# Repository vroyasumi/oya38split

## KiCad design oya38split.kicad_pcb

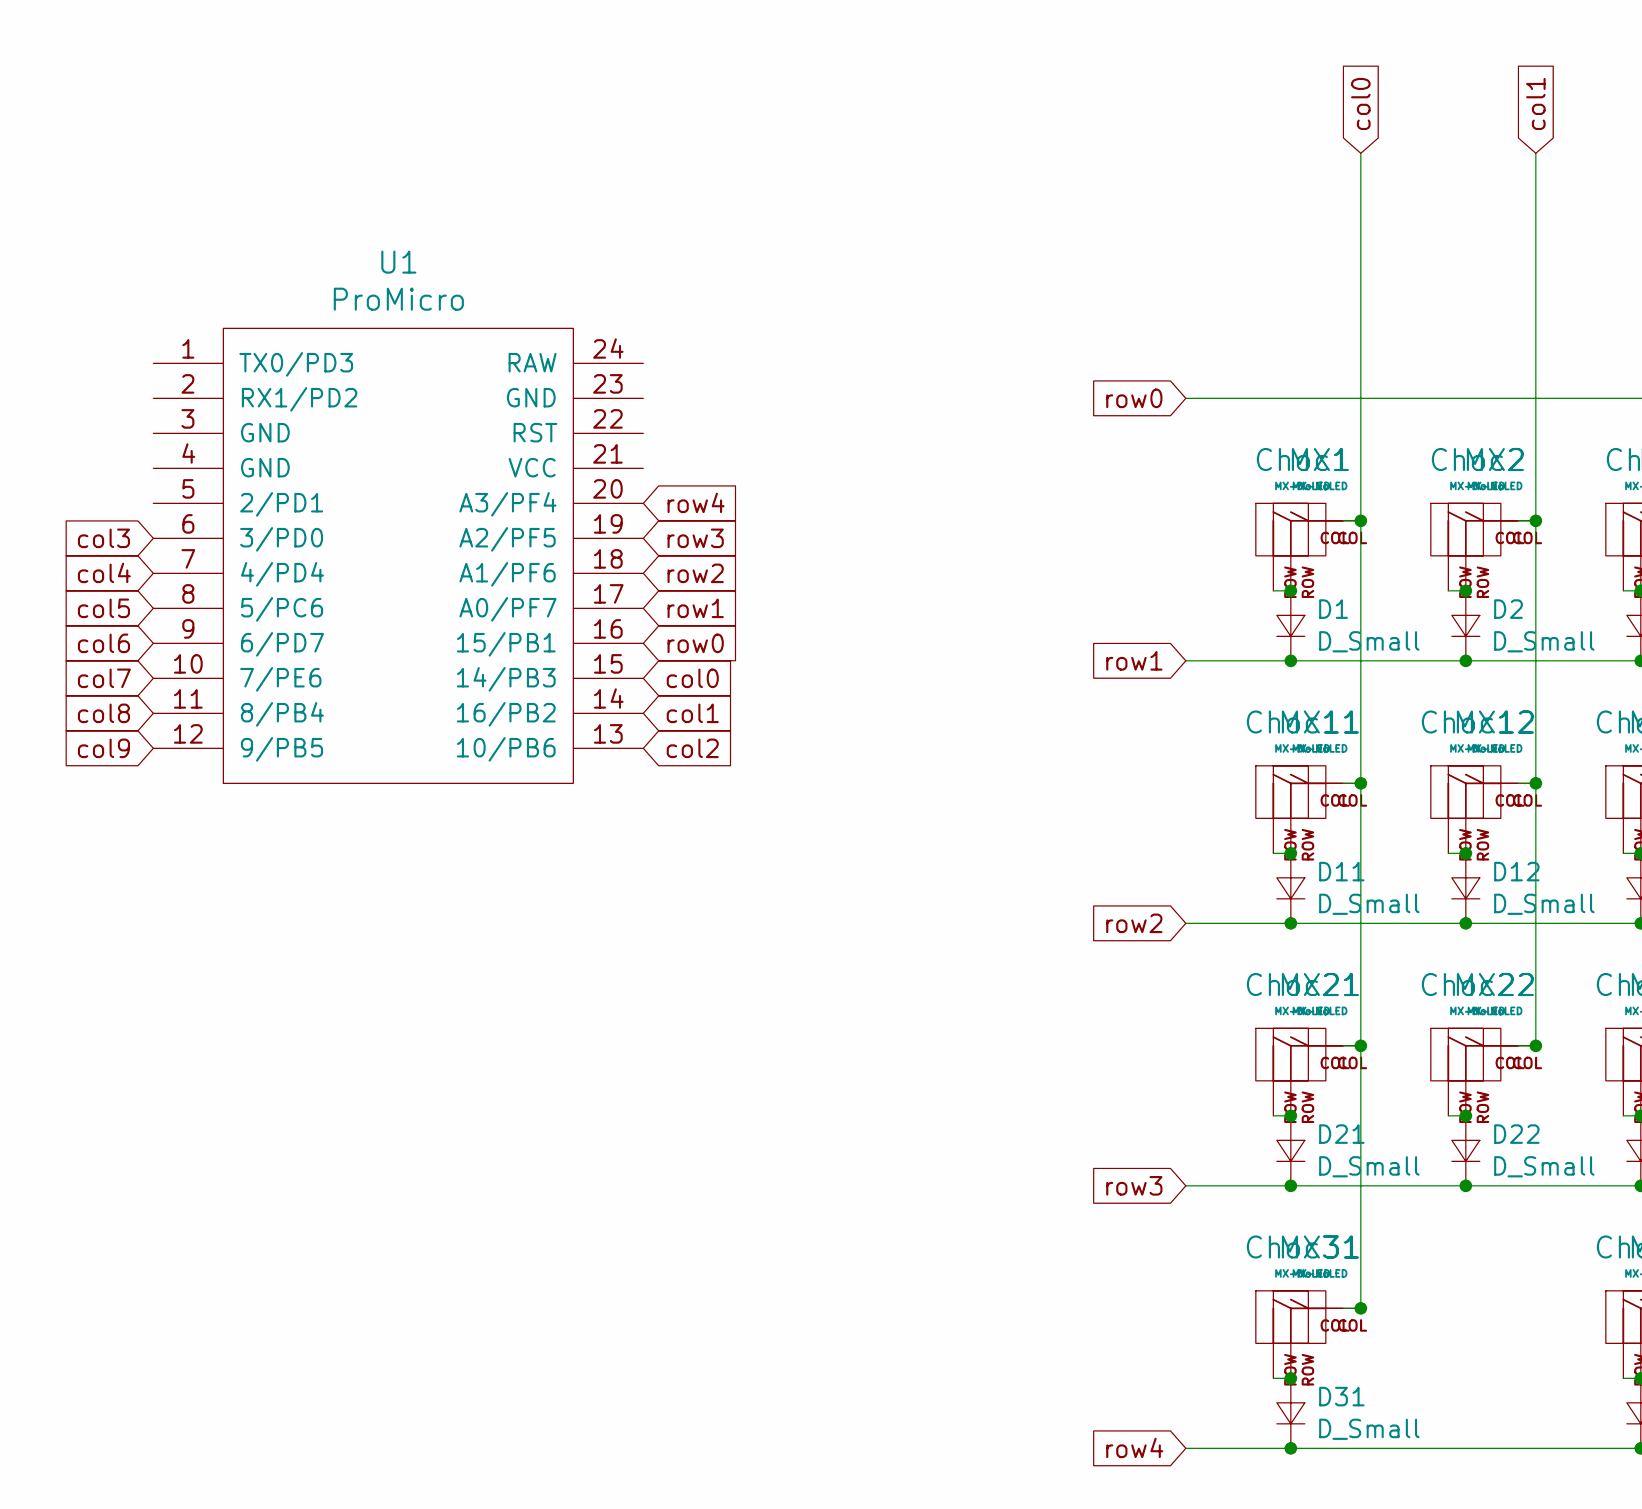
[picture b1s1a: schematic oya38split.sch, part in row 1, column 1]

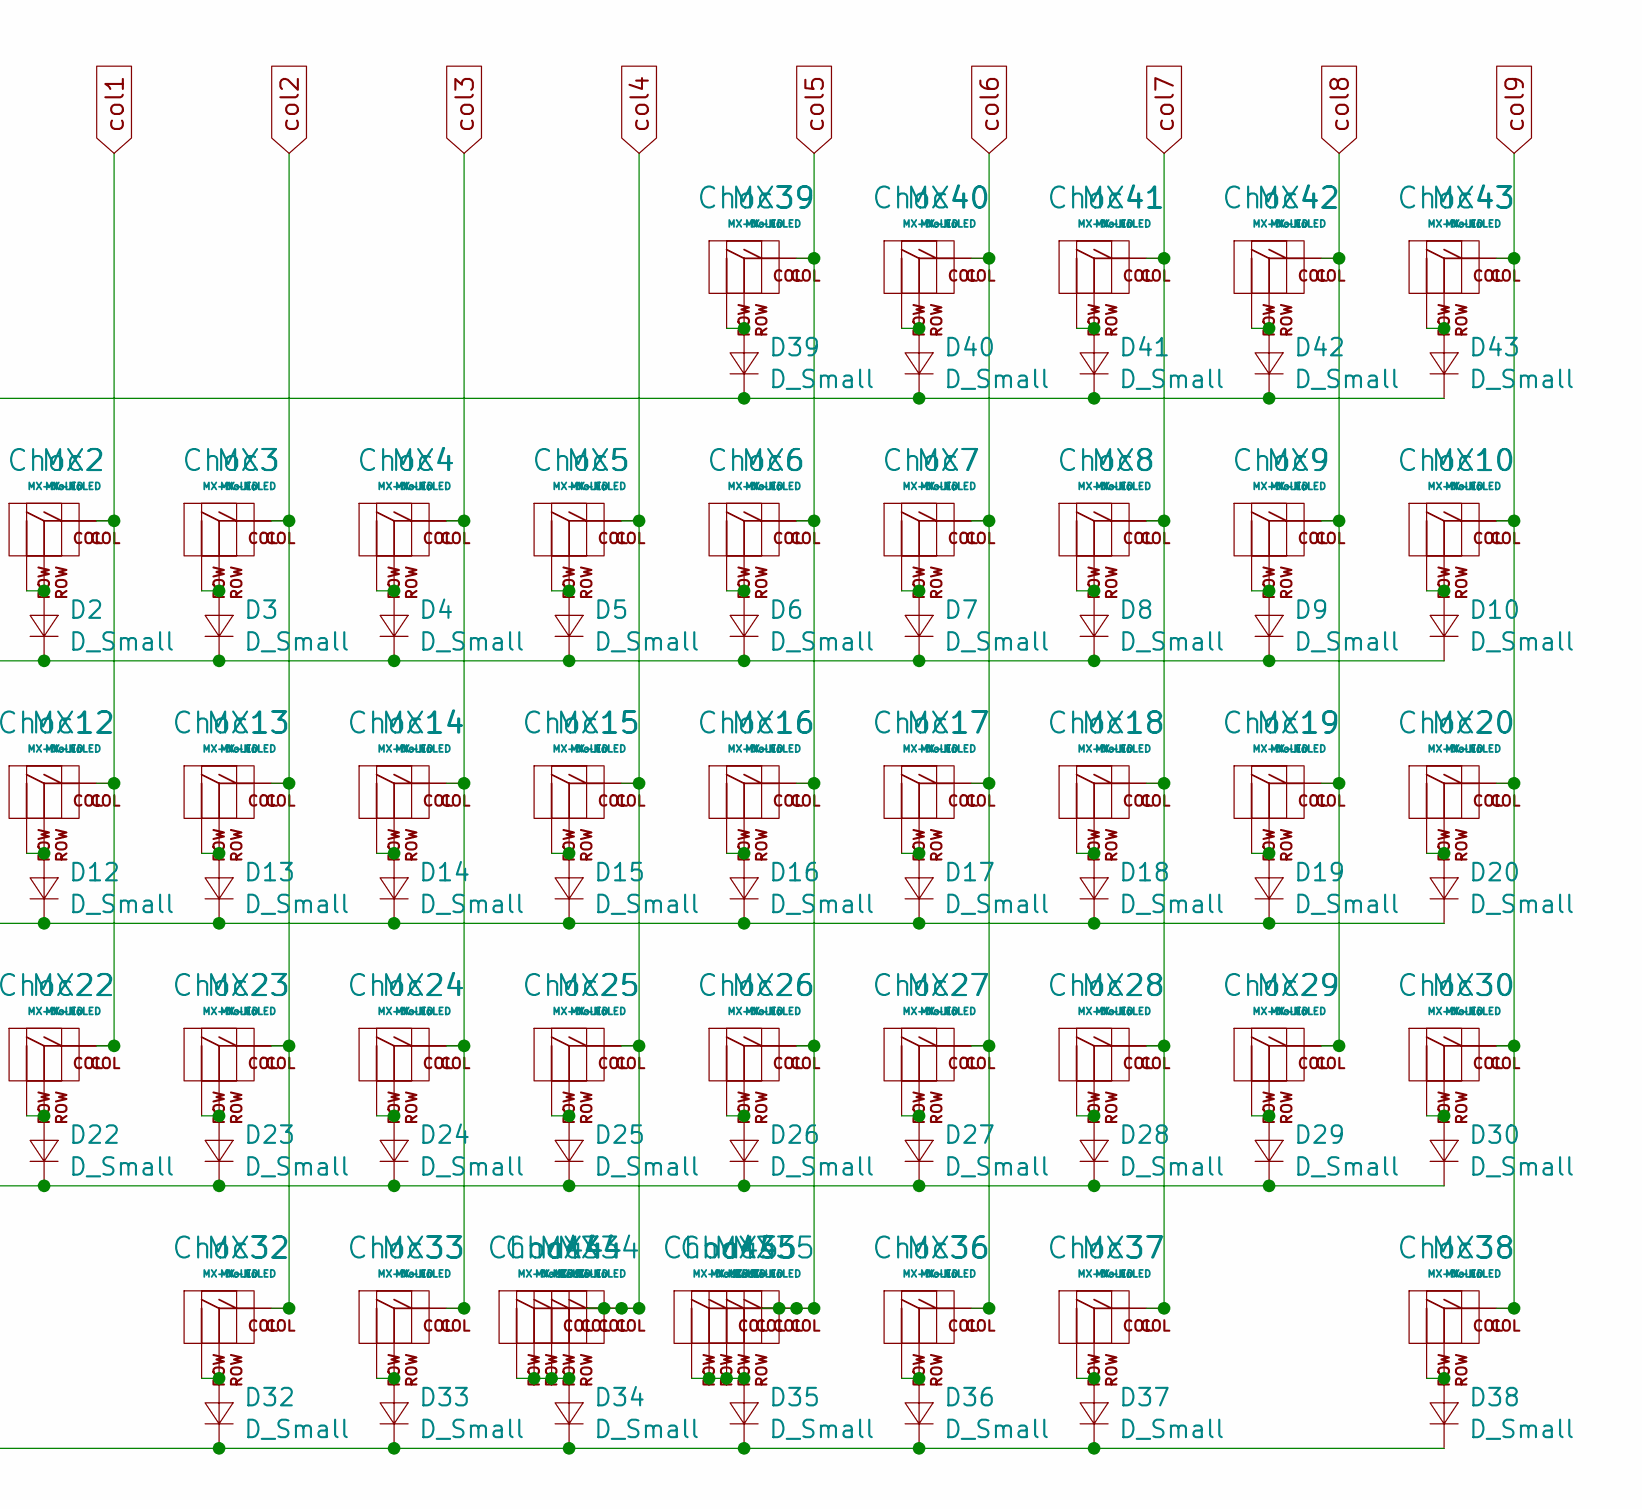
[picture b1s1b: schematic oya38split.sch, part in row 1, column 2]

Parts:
Choc1, Choc2, Choc3, Choc4, Choc5, Choc6, Choc7, Choc8, Choc9, Choc10, Choc11, Choc12, Choc13, Choc14, Choc15, Choc16, Choc17, Choc18, Choc19, Choc20, Choc21, Choc22, Choc23, Choc24, Choc25, Choc26, Choc27, Choc28, Choc29, Choc30, Choc31, Choc32, Choc33, Choc34, Choc35, Choc36, Choc37, Choc38, Choc39, Choc40, Choc41, Choc42, Choc43, Choc44, Choc45: MX-NoLED; ChocV1_V2_Hotswap
D1, D2, D3, D4, D5, D6, D7, D8, D9, D10, D11, D12, D13, D14, D15, D16, D17, D18, D19, D20, D21, D22, D23, D24, D25, D26, D27, D28, D29, D30, D31, D32, D33, D34, D35, D36, D37, D38, D39, D40, D41, D42, D43: D_Small; D_0805
MX1, MX2, MX3, MX4, MX5, MX6, MX7, MX8, MX9, MX10, MX11, MX12, MX13, MX14, MX15, MX16, MX17, MX18, MX19, MX20, MX21, MX22, MX23, MX24, MX25, MX26, MX27, MX28, MX29, MX30, MX31, MX32, MX33, MX34, MX35, MX36, MX37, MX38, MX39, MX40, MX41, MX42, MX43: MX-NoLED; MXOnly-1U-Hotswap
MX44, MX45: MX-NoLED; MXOnly-2U-Hotswap
U1: ProMicro; ArduinoProMicro-ZigZag

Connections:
unnamed: Choc1.2 (ROW), D1.2 (A), MX1.2 (ROW)
unnamed: Choc2.2 (ROW), D2.2 (A), MX2.2 (ROW)
unnamed: Choc3.2 (ROW), D3.2 (A), MX3.2 (ROW)
unnamed: Choc4.2 (ROW), D4.2 (A), MX4.2 (ROW)
unnamed: Choc5.2 (ROW), D5.2 (A), MX5.2 (ROW)
unnamed: Choc6.2 (ROW), D6.2 (A), MX6.2 (ROW)
unnamed: Choc7.2 (ROW), D7.2 (A), MX7.2 (ROW)
unnamed: Choc8.2 (ROW), D8.2 (A), MX8.2 (ROW)
unnamed: Choc9.2 (ROW), D9.2 (A), MX9.2 (ROW)
unnamed: Choc10.2 (ROW), D10.2 (A), MX10.2 (ROW)
unnamed: Choc11.2 (ROW), D11.2 (A), MX11.2 (ROW)
unnamed: Choc12.2 (ROW), D12.2 (A), MX12.2 (ROW)
unnamed: Choc13.2 (ROW), D13.2 (A), MX13.2 (ROW)
unnamed: Choc14.2 (ROW), D14.2 (A), MX14.2 (ROW)
unnamed: Choc15.2 (ROW), D15.2 (A), MX15.2 (ROW)
unnamed: Choc16.2 (ROW), D16.2 (A), MX16.2 (ROW)
unnamed: Choc17.2 (ROW), D17.2 (A), MX17.2 (ROW)
unnamed: Choc18.2 (ROW), D18.2 (A), MX18.2 (ROW)
unnamed: Choc19.2 (ROW), D19.2 (A), MX19.2 (ROW)
unnamed: Choc20.2 (ROW), D20.2 (A), MX20.2 (ROW)
unnamed: Choc21.2 (ROW), D21.2 (A), MX21.2 (ROW)
unnamed: Choc22.2 (ROW), D22.2 (A), MX22.2 (ROW)
unnamed: Choc23.2 (ROW), D23.2 (A), MX23.2 (ROW)
unnamed: Choc24.2 (ROW), D24.2 (A), MX24.2 (ROW)
unnamed: Choc25.2 (ROW), D25.2 (A), MX25.2 (ROW)
unnamed: Choc26.2 (ROW), D26.2 (A), MX26.2 (ROW)
unnamed: Choc27.2 (ROW), D27.2 (A), MX27.2 (ROW)
unnamed: Choc28.2 (ROW), D28.2 (A), MX28.2 (ROW)
unnamed: Choc29.2 (ROW), D29.2 (A), MX29.2 (ROW)
unnamed: Choc30.2 (ROW), D30.2 (A), MX30.2 (ROW)
unnamed: Choc31.2 (ROW), D31.2 (A), MX31.2 (ROW)
unnamed: Choc32.2 (ROW), D32.2 (A), MX32.2 (ROW)
unnamed: Choc33.2 (ROW), D33.2 (A), MX33.2 (ROW)
unnamed: Choc34.2 (ROW), Choc44.2 (ROW), D34.2 (A), MX34.2 (ROW), MX44.2 (ROW)
unnamed: Choc35.2 (ROW), Choc45.2 (ROW), D35.2 (A), MX35.2 (ROW), MX45.2 (ROW)
unnamed: Choc36.2 (ROW), D36.2 (A), MX36.2 (ROW)
unnamed: Choc37.2 (ROW), D37.2 (A), MX37.2 (ROW)
unnamed: Choc38.2 (ROW), D38.2 (A), MX38.2 (ROW)
unnamed: Choc39.2 (ROW), D39.2 (A), MX39.2 (ROW)
unnamed: Choc40.2 (ROW), D40.2 (A), MX40.2 (ROW)
unnamed: Choc41.2 (ROW), D41.2 (A), MX41.2 (ROW)
unnamed: Choc42.2 (ROW), D42.2 (A), MX42.2 (ROW)
unnamed: Choc43.2 (ROW), D43.2 (A), MX43.2 (ROW)
col0: Choc1.1 (COL), Choc11.1 (COL), Choc21.1 (COL), Choc31.1 (COL), MX1.1 (COL), MX11.1 (COL), MX21.1 (COL), MX31.1 (COL), U1.15 (14/PB3)
col1: Choc2.1 (COL), Choc12.1 (COL), Choc22.1 (COL), MX2.1 (COL), MX12.1 (COL), MX22.1 (COL), U1.14 (16/PB2)
col2: Choc3.1 (COL), Choc13.1 (COL), Choc23.1 (COL), Choc32.1 (COL), MX3.1 (COL), MX13.1 (COL), MX23.1 (COL), MX32.1 (COL), U1.13 (10/PB6)
col3: Choc4.1 (COL), Choc14.1 (COL), Choc24.1 (COL), Choc33.1 (COL), MX4.1 (COL), MX14.1 (COL), MX24.1 (COL), MX33.1 (COL), U1.6 (3/PD0)
col4: Choc5.1 (COL), Choc15.1 (COL), Choc25.1 (COL), Choc34.1 (COL), Choc44.1 (COL), MX5.1 (COL), MX15.1 (COL), MX25.1 (COL), MX34.1 (COL), MX44.1 (COL), U1.7 (4/PD4)
col5: Choc6.1 (COL), Choc16.1 (COL), Choc26.1 (COL), Choc35.1 (COL), Choc39.1 (COL), Choc45.1 (COL), MX6.1 (COL), MX16.1 (COL), MX26.1 (COL), MX35.1 (COL), MX39.1 (COL), MX45.1 (COL), U1.8 (5/PC6)
col6: Choc7.1 (COL), Choc17.1 (COL), Choc27.1 (COL), Choc36.1 (COL), Choc40.1 (COL), MX7.1 (COL), MX17.1 (COL), MX27.1 (COL), MX36.1 (COL), MX40.1 (COL), U1.9 (6/PD7)
col7: Choc8.1 (COL), Choc18.1 (COL), Choc28.1 (COL), Choc37.1 (COL), Choc41.1 (COL), MX8.1 (COL), MX18.1 (COL), MX28.1 (COL), MX37.1 (COL), MX41.1 (COL), U1.10 (7/PE6); also elsewhere on the board
col8: Choc9.1 (COL), Choc19.1 (COL), Choc29.1 (COL), Choc42.1 (COL), MX9.1 (COL), MX19.1 (COL), MX29.1 (COL), MX42.1 (COL), U1.11 (8/PB4)
col9: Choc10.1 (COL), Choc20.1 (COL), Choc30.1 (COL), Choc38.1 (COL), Choc43.1 (COL), MX10.1 (COL), MX20.1 (COL), MX30.1 (COL), MX38.1 (COL), MX43.1 (COL), U1.12 (9/PB5)
row0: D39.1 (K), D40.1 (K), D41.1 (K), D42.1 (K), D43.1 (K), U1.16 (15/PB1)
row1: D1.1 (K), D2.1 (K), D3.1 (K), D4.1 (K), D5.1 (K), D6.1 (K), D7.1 (K), D8.1 (K), D9.1 (K), D10.1 (K), U1.17 (A0/PF7)
row2: D11.1 (K), D12.1 (K), D13.1 (K), D14.1 (K), D15.1 (K), D16.1 (K), D17.1 (K), D18.1 (K), D19.1 (K), D20.1 (K), U1.18 (A1/PF6)
row3: D21.1 (K), D22.1 (K), D23.1 (K), D24.1 (K), D25.1 (K), D26.1 (K), D27.1 (K), D28.1 (K), D29.1 (K), D30.1 (K), U1.19 (A2/PF5)
row4: D31.1 (K), D32.1 (K), D33.1 (K), D34.1 (K), D35.1 (K), D36.1 (K), D37.1 (K), D38.1 (K), U1.20 (A3/PF4)

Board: 2 copper layers, 135 parts (65 on the bottom side), 58 nets, no tracks yet.

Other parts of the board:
SW1: Rotary_Encoder_Switch; RollerEncoder_Panasonic_EVQWGD001

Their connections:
col7: SW1.S2; also elsewhere on the board

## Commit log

2021-09-13 added sch and pcb file
2021-09-13 Add submodules
2021-09-13 added pretty
2021-09-13 Added footprints
2021-09-13 named mx in sch
2021-09-13 fixed schematics
2021-09-13 named diodes
2021-09-13 added some of the schematics
2021-09-13 added sch to pcb
2021-09-13 fixed diode alignment
2021-09-13 fixing diodes and adding split
2021-09-13 organized layout
2021-09-13 added pro micro location
2021-09-13 added edge cuts and moved pro micro
2021-09-13 added traces
2021-09-13 test
2021-09-13 layout
2021-09-13 fixed orientation
2021-09-13 fixed pcb layout
2021-09-13 final layout
2021-09-13 added diode traces
2021-09-13 added column tracks
2021-09-13 added column and diode traces
2021-09-13 added column and diode tracks
2021-09-13 named col and rows
2021-09-13 added promicro naming
2021-09-13 added tracks but not final
2021-09-15 changed layout idea
2021-09-15 fixed layout
2021-09-15 fixed edgecut
2021-09-15 arranged diodes
2021-09-15 fixed diodes with normal layout
2021-09-15 places diodes with switches
2021-09-15 placed everything
2021-09-15 added traces and fixed diode
2021-09-15 fixed diode placement
2021-09-15 added solder mask and gnd fill
2021-09-15 finalized the first run
2021-09-15 cleaned up routing
2021-09-15 rearranged some diode tracks
2021-09-16 fixed diode lines
2021-09-16 fixed traces
2021-09-16 fixed diodes and traces
2021-09-16 added gerbers
2021-09-16 fixed pcb
2021-09-16 finalized pcb and added gerbers
2021-09-16 created plate cutouts
2021-09-16 fixed numrow
2021-09-16 finished pcb and plate
2021-09-16 fixed tracing
2021-09-16 final pcb and plate
2021-09-16 testing out layout
2021-09-17 made switch plate
2021-09-17 added pcb and plate gerbers
2021-09-17 final pcb gerbers
2021-09-17 save
2021-09-17 fixed traces and added gerbers
2021-09-18 final pcb and gerbers
2021-10-06 fixed diode trace
2021-10-08 added breakout
2021-10-08 added encoder
2021-10-09 added rotary encoder
2021-10-09 cache
2021-10-10 changing pcb
2021-10-10 added choc support
2021-10-11 added choc footprint
